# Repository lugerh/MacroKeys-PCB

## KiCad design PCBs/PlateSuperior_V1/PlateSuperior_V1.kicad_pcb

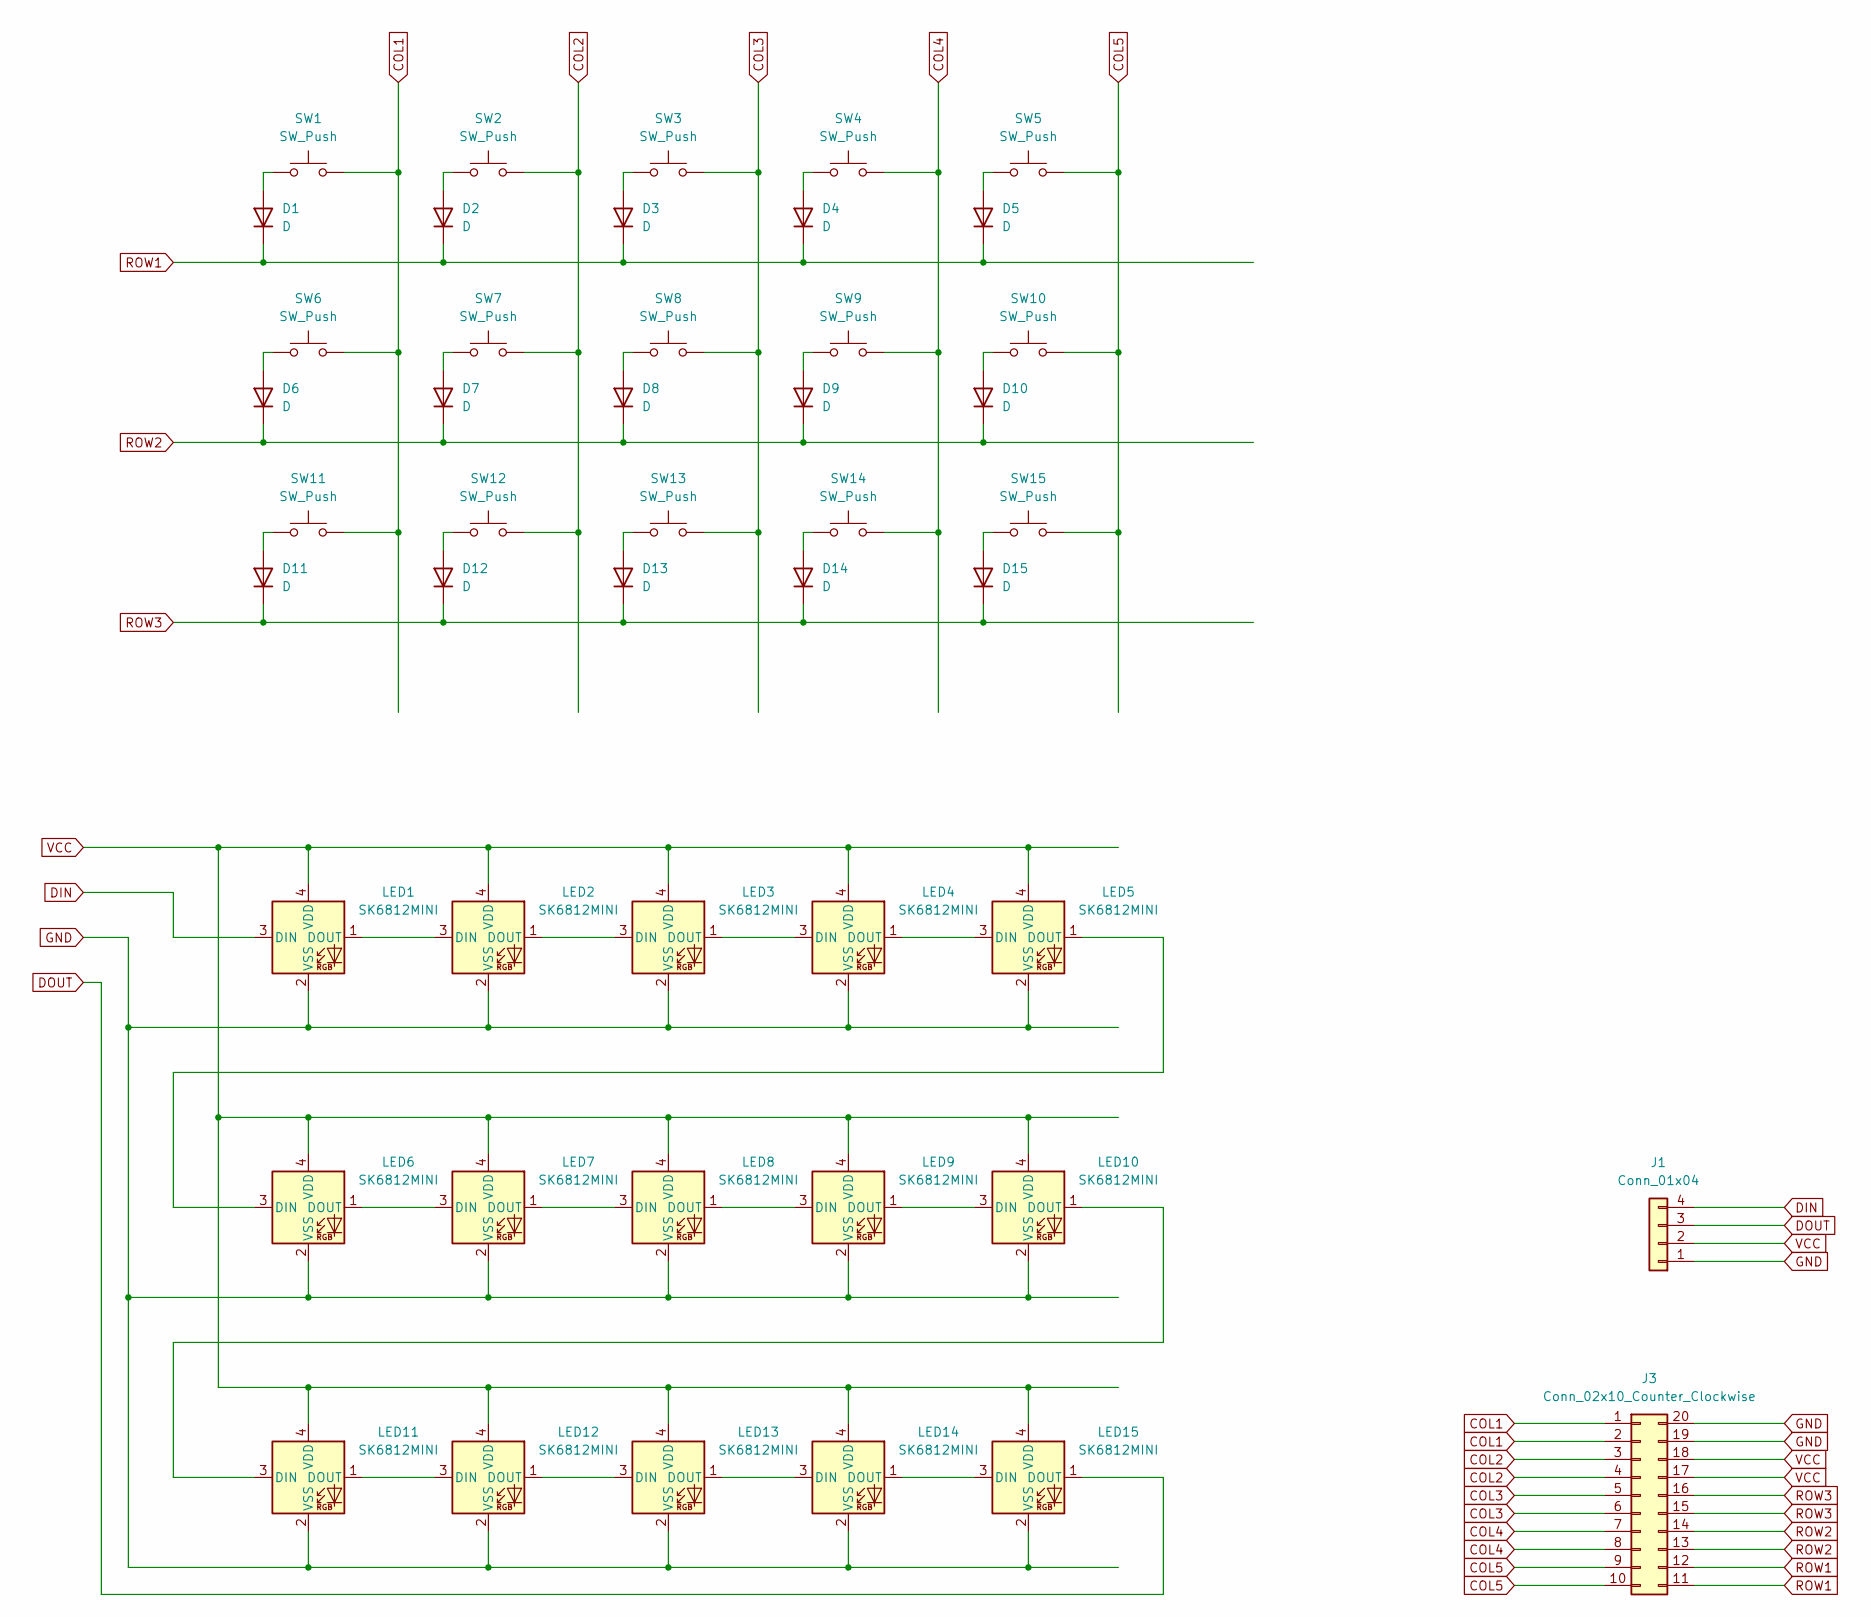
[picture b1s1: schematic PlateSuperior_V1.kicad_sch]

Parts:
D1, D2, D3, D4, D5, D6, D7, D8, D9, D10, D11, D12, D13, D14, D15: D; D_0603_1608Metric
J1: Conn_01x04
J3: Conn_02x10_Counter_Clockwise; PinHeader_2x10_P2.54mm_Vertical
LED1, LED2, LED3, LED4, LED5, LED6, LED7, LED8, LED9, LED10, LED11, LED12, LED13, LED14, LED15: SK6812MINI; SK6812 MINI W_hole
SW1, SW6, SW11: SW_Push; MX-Hotswap-1.25U
SW2, SW3, SW4, SW5, SW7, SW8, SW9, SW10, SW12, SW13, SW14, SW15: SW_Push; MX-Hotswap-1U

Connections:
COL1: J3.1, J3.2, SW1.2, SW6.2, SW11.2
COL2: J3.3, J3.4, SW2.2, SW7.2, SW12.2
COL3: J3.5, J3.6, SW3.2, SW8.2, SW13.2
COL4: J3.7, J3.8, SW4.2, SW9.2, SW14.2
COL5: J3.9, J3.10, SW5.2, SW10.2, SW15.2
DIN: J1.4, LED1.3 (DIN)
DOUT: J1.3, LED15.1 (DOUT)
GND: J1.1, J3.19, J3.20, LED1.2 (VSS), LED2.2 (VSS), LED3.2 (VSS), LED4.2 (VSS), LED5.2 (VSS), LED6.2 (VSS), LED7.2 (VSS), LED8.2 (VSS), LED9.2 (VSS), LED10.2 (VSS), LED11.2 (VSS), LED12.2 (VSS), LED13.2 (VSS), LED14.2 (VSS), LED15.2 (VSS)
unnamed: D1.2 (A), SW1.1
unnamed: D2.2 (A), SW2.1
unnamed: D3.2 (A), SW3.1
unnamed: D4.2 (A), SW4.1
unnamed: D5.2 (A), SW5.1
unnamed: D6.2 (A), SW6.1
unnamed: D7.2 (A), SW7.1
unnamed: D8.2 (A), SW8.1
unnamed: D9.2 (A), SW9.1
unnamed: D10.2 (A), SW10.1
unnamed: D11.2 (A), SW11.1
unnamed: D12.2 (A), SW12.1
unnamed: D13.2 (A), SW13.1
unnamed: D14.2 (A), SW14.1
unnamed: D15.2 (A), SW15.1
unnamed: LED1.1 (DOUT), LED2.3 (DIN)
unnamed: LED2.1 (DOUT), LED3.3 (DIN)
unnamed: LED3.1 (DOUT), LED4.3 (DIN)
unnamed: LED4.1 (DOUT), LED5.3 (DIN)
unnamed: LED5.1 (DOUT), LED6.3 (DIN)
unnamed: LED6.1 (DOUT), LED7.3 (DIN)
unnamed: LED7.1 (DOUT), LED8.3 (DIN)
unnamed: LED8.1 (DOUT), LED9.3 (DIN)
unnamed: LED9.1 (DOUT), LED10.3 (DIN)
unnamed: LED10.1 (DOUT), LED11.3 (DIN)
unnamed: LED11.1 (DOUT), LED12.3 (DIN)
unnamed: LED12.1 (DOUT), LED13.3 (DIN)
unnamed: LED13.1 (DOUT), LED14.3 (DIN)
unnamed: LED14.1 (DOUT), LED15.3 (DIN)
ROW1: D1.1 (K), D2.1 (K), D3.1 (K), D4.1 (K), D5.1 (K), J3.11, J3.12
ROW2: D6.1 (K), D7.1 (K), D8.1 (K), D9.1 (K), D10.1 (K), J3.13, J3.14
ROW3: D11.1 (K), D12.1 (K), D13.1 (K), D14.1 (K), D15.1 (K), J3.15, J3.16
VCC: J1.2, J3.17, J3.18, LED1.4 (VDD), LED2.4 (VDD), LED3.4 (VDD), LED4.4 (VDD), LED5.4 (VDD), LED6.4 (VDD), LED7.4 (VDD), LED8.4 (VDD), LED9.4 (VDD), LED10.4 (VDD), LED11.4 (VDD), LED12.4 (VDD), LED13.4 (VDD), LED14.4 (VDD), LED15.4 (VDD)

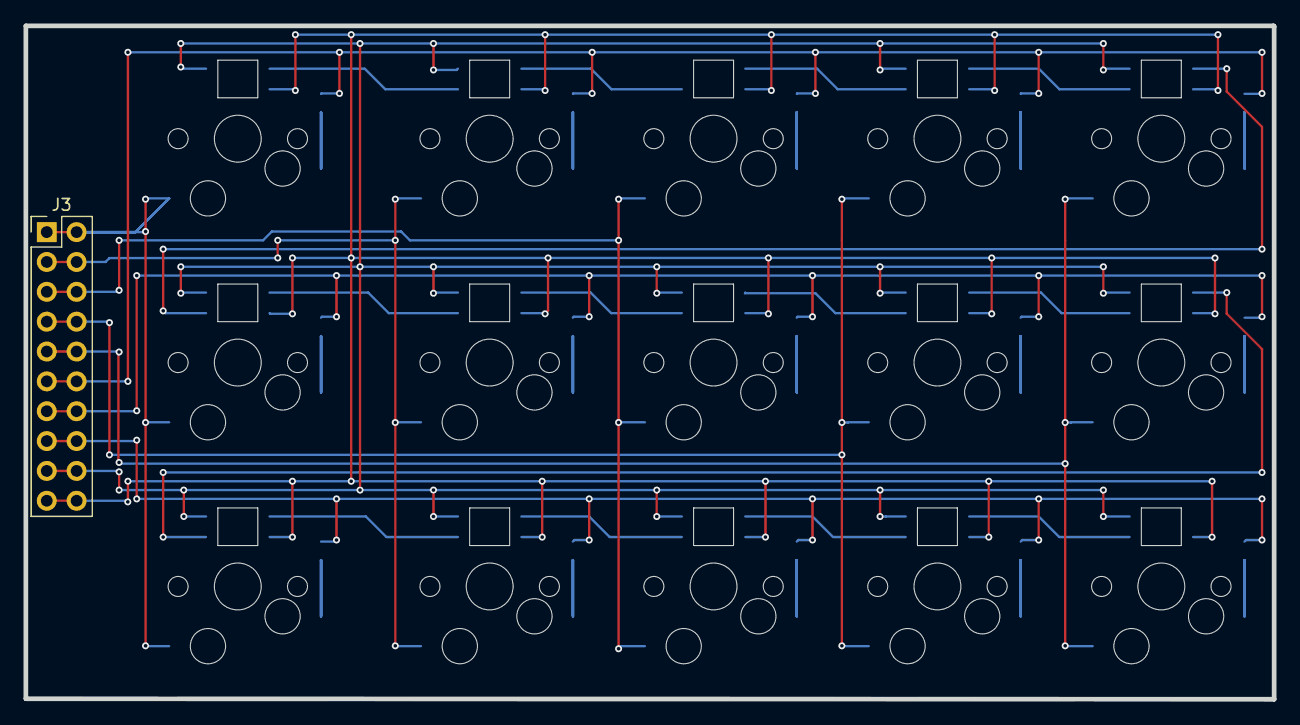
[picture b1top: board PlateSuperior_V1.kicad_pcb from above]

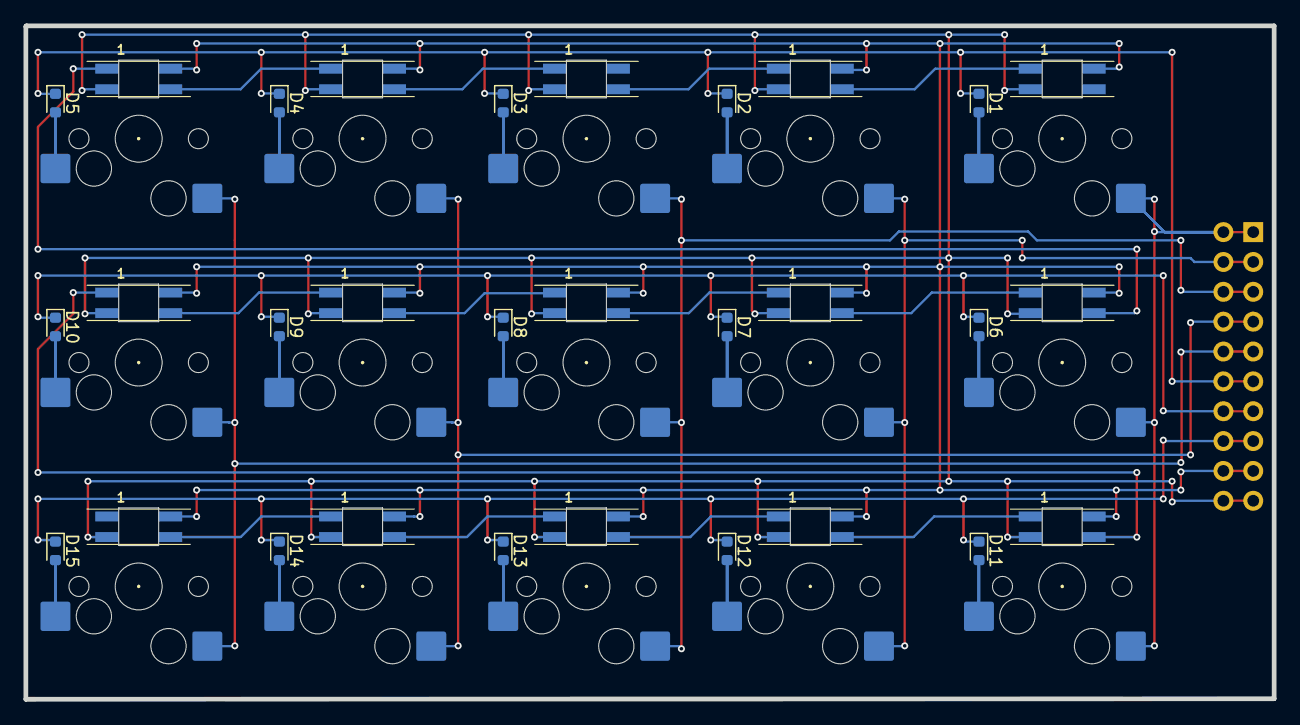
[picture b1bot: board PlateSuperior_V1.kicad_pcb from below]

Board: 2 copper layers, 106.2 x 57.3 mm, 46 parts (45 on the bottom side), 39 nets.

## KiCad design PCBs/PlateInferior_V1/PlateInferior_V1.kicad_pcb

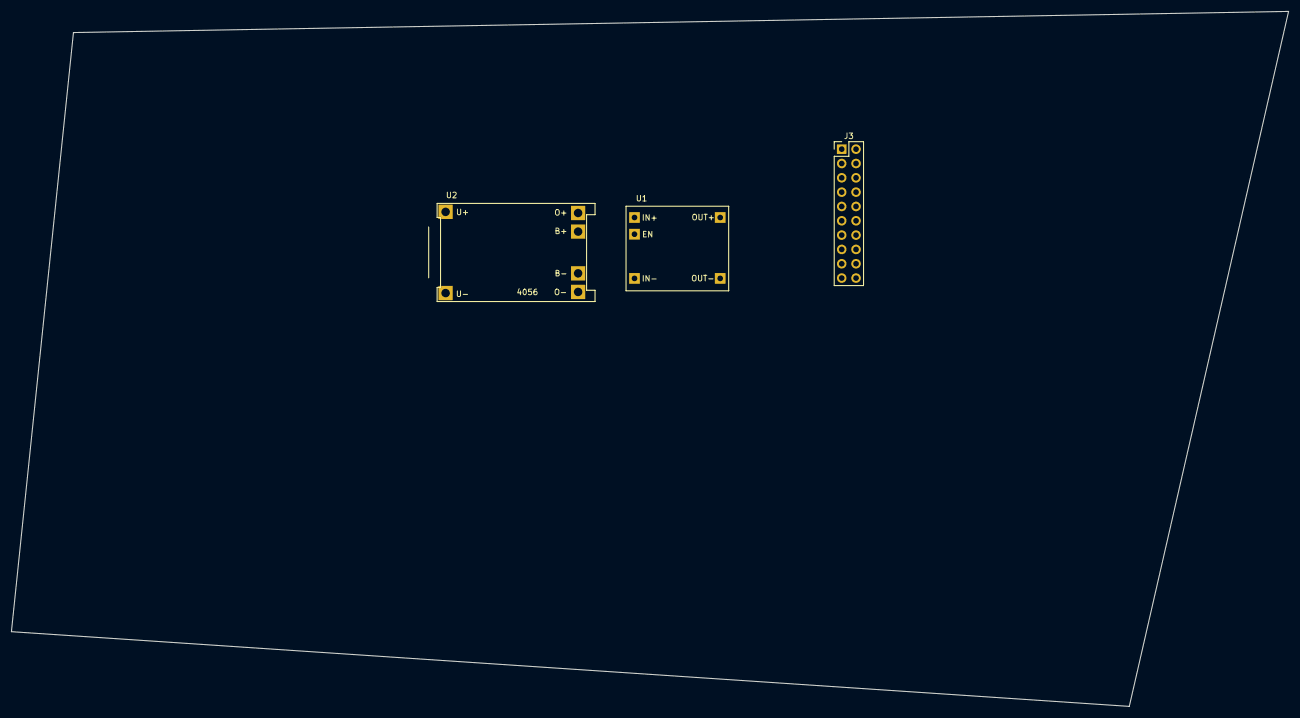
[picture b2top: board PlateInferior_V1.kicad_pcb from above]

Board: 2 copper layers, 226.5 x 123.2 mm, 3 parts (0 on the bottom side), 11 nets, no tracks yet.

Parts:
J3: Conn_02x10_Counter_Clockwise; PinHeader_2x10_P2.54mm_Vertical
U1: dcdc_Var_5W
U2: TPS4056 Board

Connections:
COL1: J3.1, J3.2
COL2: J3.3, J3.4
COL3: J3.5, J3.6
COL4: J3.7, J3.8
COL5: J3.9, J3.10
GND: J3.19, J3.20, U1.2 (IN-), U1.4 (OUT-), U2.6 (OUT-)
ROW1: J3.11, J3.12
ROW2: J3.13, J3.14
ROW3: J3.15, J3.16
VBAT_BMS: U1.1 (IN+), U1.5 (En), U2.3 (OUT+)
VCC: J3.17, J3.18, U1.3 (OUT+)

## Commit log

2025-03-08 First draft, keyboard layout power!!
2025-03-30 Add plates
2025-04-12 Add top PCB
2025-05-08 Add Test codes ESP32 & ESP32S3
